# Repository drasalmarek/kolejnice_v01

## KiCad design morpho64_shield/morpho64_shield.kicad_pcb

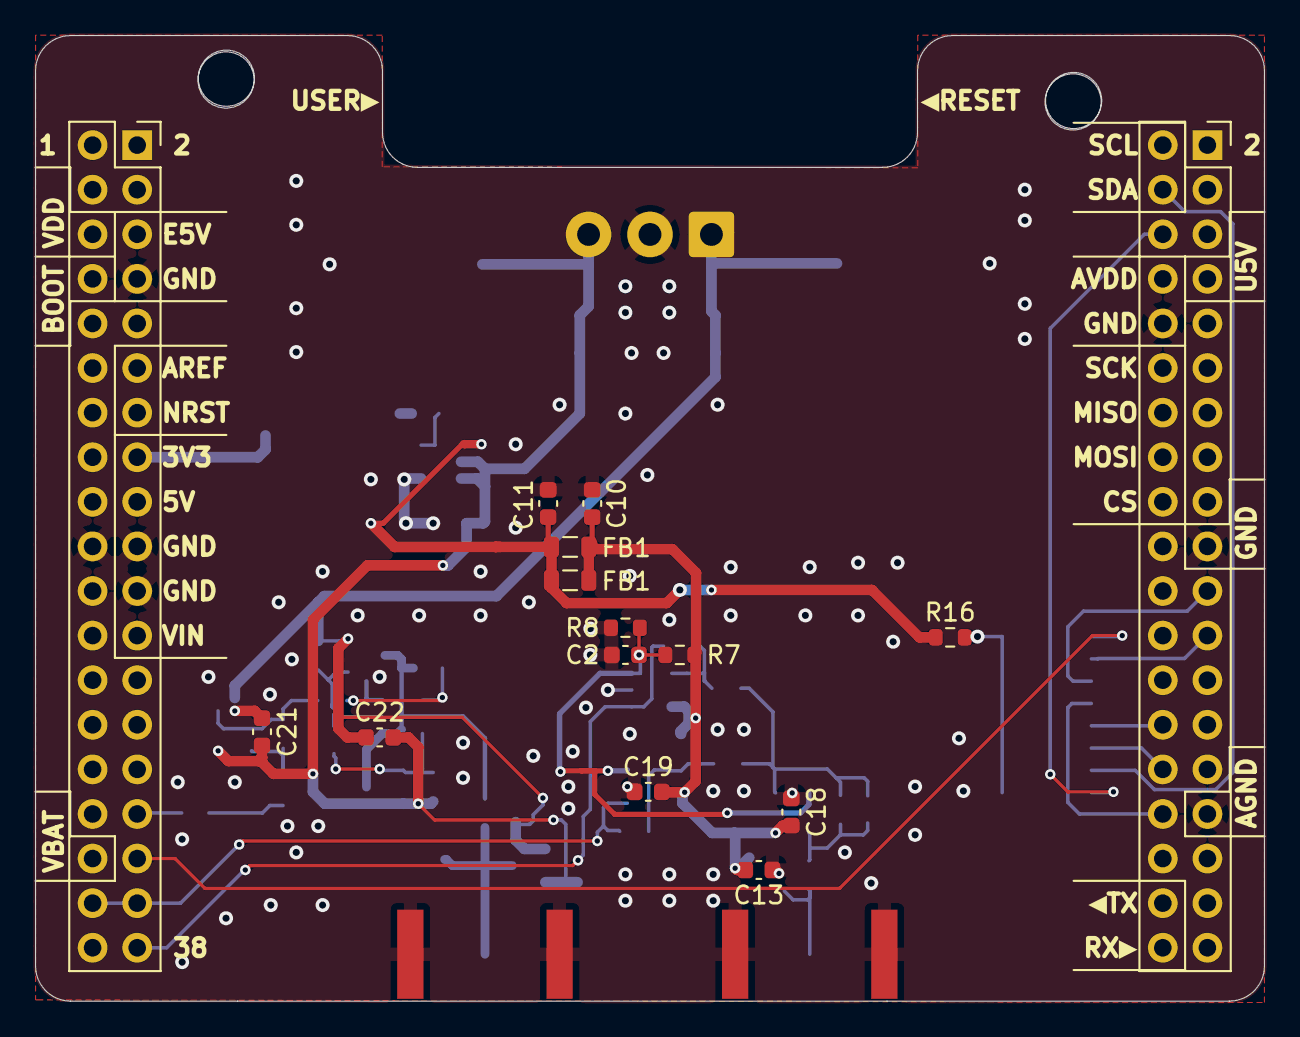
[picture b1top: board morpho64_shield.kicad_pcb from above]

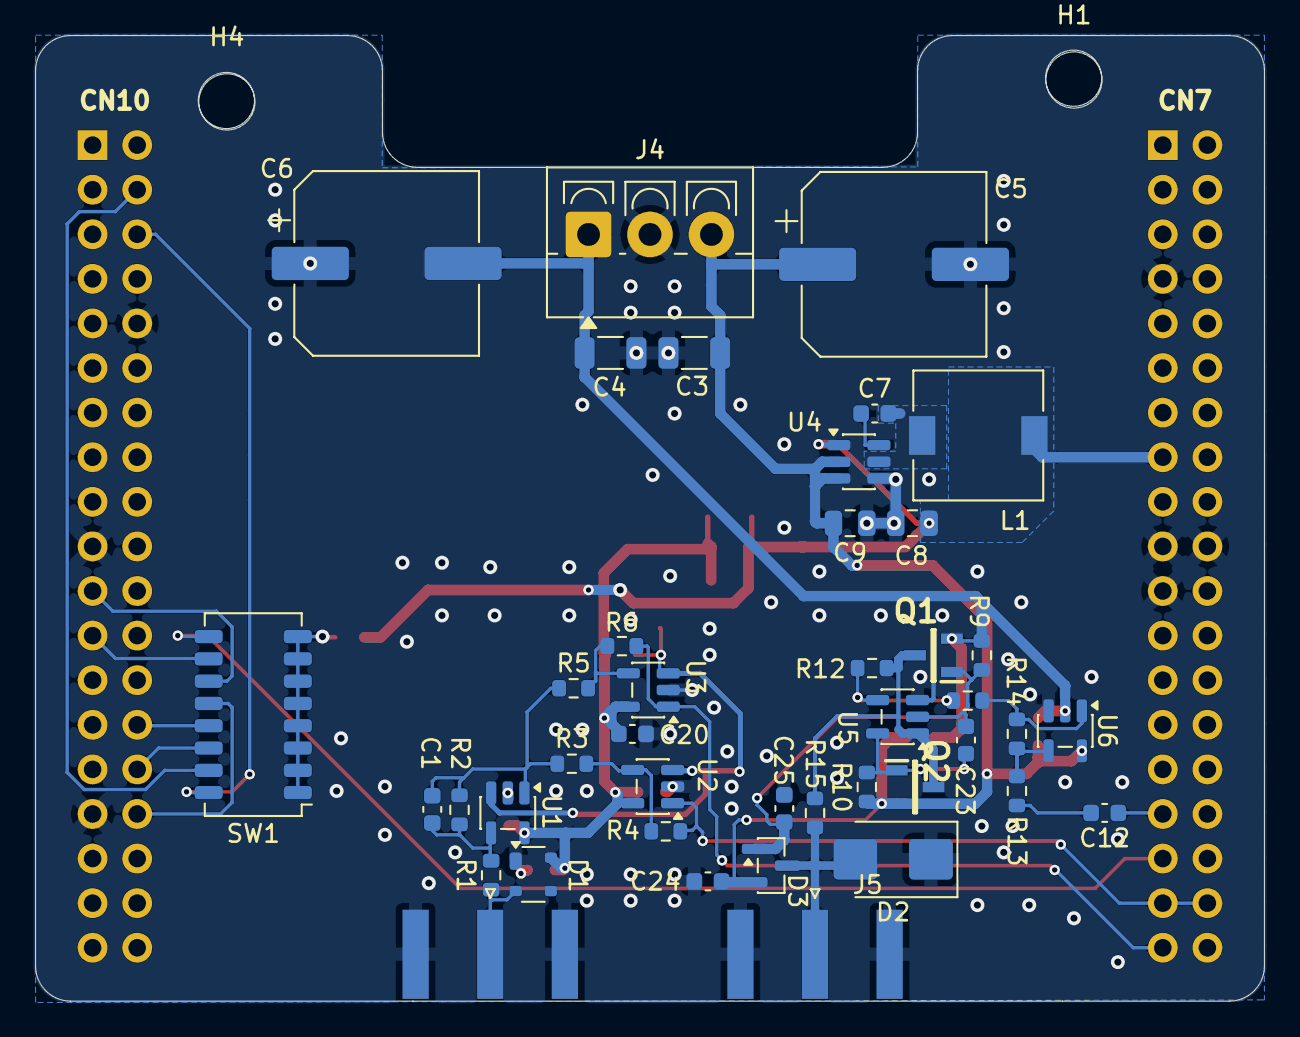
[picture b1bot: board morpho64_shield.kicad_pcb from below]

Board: 4 copper layers, 70.0 x 55.0 mm, 62 parts (44 on the bottom side), 34 nets.

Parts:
C1, C12: C; C_0603_1608Metric
C2, C7, C10, C11, C13, C18, C19, C20, C21, C22, C24, C25: 100nF; C_0603_1608Metric
C3, C4: 22uF; C_1206_3216Metric
C5, C6: 470uF; CP_Elec_10x7.7
C8: 22uF; C_0805_2012Metric
C9: 10uF; C_0805_2012Metric
C23: DNP; C_0603_1608Metric
D1: PRTR5V0U2X; SOT-143
D2: SMBJ24CA; D_SMB
D3: BAT54S; SOT-23
FB1, FB1#2: FerriteBead; L_0805_2012Metric
H1, H2, H3, H4: MountingHole; MountingHole_3.2mm_M3_ISO14580
J1: CN7; PinSocket_2x19_P2.54mm_Vertical
J2: CN10; PinSocket_2x19_P2.54mm_Vertical
J3, J5: Conn_Coaxial_Small; SMA_Amphenol_132289_EdgeMount
J4: Screw_Terminal_01x03; TerminalBlock_4Ucon_1x03_P3.50mm_Vertical
L1: 4.7uH; L_7.3x7.3_H4.5
NT1: NetTie_2; NetTie-2_SMD_Pad0.5mm
Q1: FMMT493TC; SOT95P237X112-3N
Q2: FMMT593TC; SOT95P237X112-3N
R1, R2, R3, R4, R5, R6, R9, R10, R11, R12, R13, R14, R16: R; R_0603_1608Metric
R7, R8: 1k; R_0603_1608Metric
R15: DNP; R_0603_1608Metric
SW1: SW_DIP_x08; SW_DIP_SPSTx08_Slide_Copal_CHS-08A_W5.08mm_P1.27mm_JPin
U1, U2, U3: ADA4505-1ARJZ-R7; SOT-23-5
U4: AP63203WU; TSOT-23-6
U5, U6: OPA596DBVR; SOT-23-5

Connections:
+1V8_A: C2.2, R7.1, R8.2, U1.3 (+), U2.3 (+), U3.3 (+)
+3V3: C8.2, C11.2, FB1.1, FB1#2.1, J1.15, L1.1, NT1.2, R16.1
+3V3_A: C10.2, C13.2, C18.2, C19.2, C20.2, D1.4 (VCC), FB1.2, FB1#2.2, R7.2, U1.5 (V+), U2.5 (V+), U3.5 (V+)
+24V: C3.1, C5.1, C9.2, C21.2, C22.2, C24.2, D3.2 (K), J4.3, Q2.2 (E), R10.1, U4.2 (EN), U4.3 (IN), U6.5 (V+)
-24V: C4.2, C6.2, C21.1, C22.1, C25.2, D3.1 (A), J4.1, Q1.2 (E), R9.2, U6.2 (V-)
/analog_input/IN_Q: D1.2 (I/O1), J3.1 (In), R1.1
/analog_input/IN_U: C1.2, R2.2, R3.1, R5.1, U1.1
/analog_output/U5_VCC: C23.2, Q2.1 (B), R10.2, U5.5 (V+)
/analog_output/U5_VEE: C23.1, Q1.1 (B), R9.1, U5.2 (V-)
/power/3V3_FB: NT1.1, U4.1 (FB)
/power/SW: C7.2, L1.2, U4.5 (SW)
/shield/PB0: J1.33, SW1.9
/shield/PB1: J2.23, SW1.10
/shield/PB2: J2.21, SW1.11
/shield/PB3: J2.32, SW1.12
/shield/PB4: J2.28, SW1.13
/shield/PB5: J2.30, SW1.14
/shield/PB6: J2.4, SW1.15
/shield/PB7: J2.6, SW1.16
ADC1_in: J1.37, R6.2, U3.1
ADC2_in: J1.35, J1.36, R4.2, U2.1
DAC_out: C12.1, J1.31
GND: C2.1, C3.2, C4.1, C5.2, C6.1, C8.1, C9.1, C10.1, C11.1, C13.1, C18.1, C19.1, C20.1, C24.1, C25.1, D1.1 (GND), D2.1 (A1), J1.7, J1.19, J1.20, J1.21, J2.10, J2.19, J2.31, J3.2 (Ext), J4.2, J5.2 (Ext), R8.1, U1.2 (V-), U2.2 (V-), U3.2 (V-), U4.4 (GND), U5.3 (+), U6.3 (+)
unnamed: C12.2, R13.2
unnamed: D2.2 (A2), D3.3 (COM), J5.1 (In), R15.1
unnamed: Q1.3 (C), Q2.3 (C), R12.1, R15.2, U5.1
unnamed: R11.2, R14.1, U6.1
unnamed: R16.2, SW1.1, SW1.2, SW1.3, SW1.4, SW1.5, SW1.6, SW1.7, SW1.8
unnamed: C1.1, R1.2, R2.1, U1.4 (-)
unnamed: R3.2, R4.1, U2.4 (-)
unnamed: R5.2, R6.1, U3.4 (-)
unnamed: C7.1, U4.6 (BST)
unnamed: R11.1, R12.2, U5.4 (-)
unnamed: R13.1, R14.2, U6.4 (-)
